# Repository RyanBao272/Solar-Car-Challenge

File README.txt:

SOLAR CAR TELEMETRY - SEAGULL SOLAR RACING

Live telemetry and low-voltage electronics for Staten Island Tech's solar
car at the 2026 Solar Car Challenge in Texas.

Result: 2nd place, Classic Division - 2026 Solar Car Challenge (460 miles)

HOW THE TELEMETRY WORKS
Motor controller --> Teensy 4.1 --> ESP32 --> driver LCD + Wi-Fi dashboard

code/teensyfulltelemtry
  - Reads the Fardriver motor controller over UART (19200 baud)
  - Decodes RPM, battery voltage, and current from its binary frames
  - Calculates speed and battery % from the controller's settings
  - Sends the data to the ESP32 as JSON 10 times a second

code/esp32telemetrydisplay
  - Shows the data on the driver's LCD in the steering wheel
  - Hosts a Wi-Fi dashboard that updates live over a WebSocket

CAR LOW-VOLTAGE SYSTEM (kicad-schematics/)
Full schematic: kicad-schematics/solar schematic.pdf

  - 24V aux battery, fuse block, 24V to 5V converter, fan, camera
  - Disconnect switches and contactors for the 96V motor and solar array
  - Front and back Arduinos talking over CAN for lights, horn, and signals

Telemetry PCB: teensy.kicad_sch / teensy.kicad_pcb
  (Teensy 4.1, ESP32, RS485-to-TTL converter, buck converter)

PHOTOS AND VIDEOS
See the images/ folder.

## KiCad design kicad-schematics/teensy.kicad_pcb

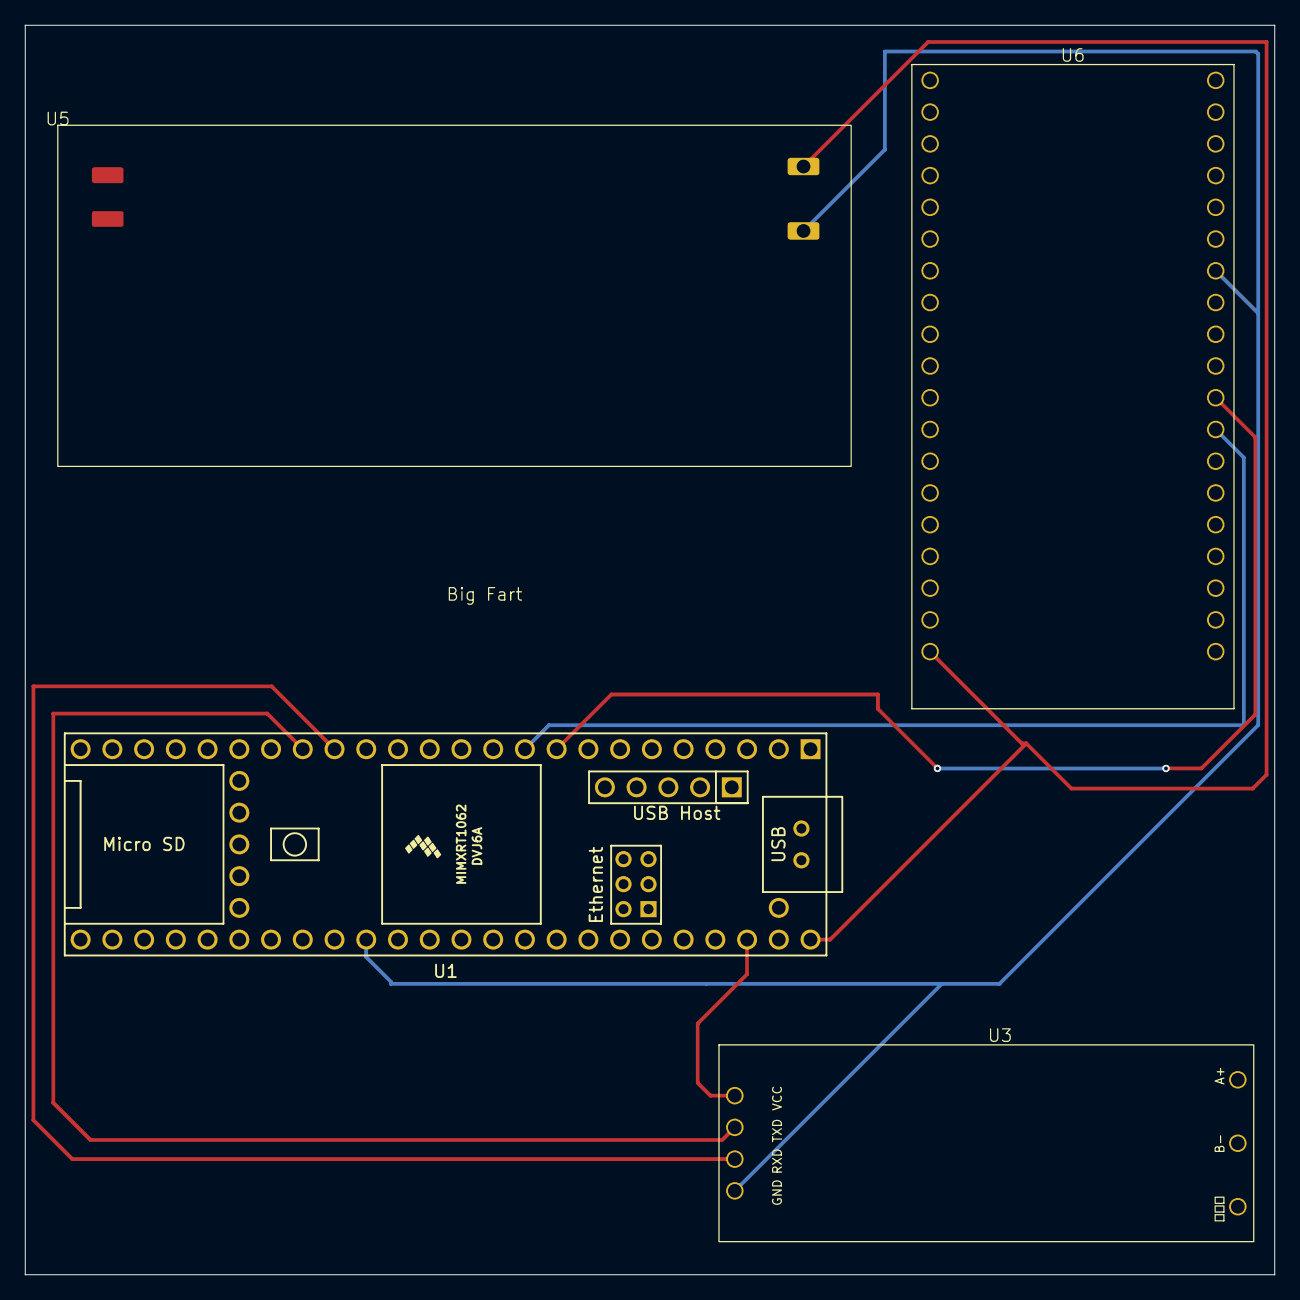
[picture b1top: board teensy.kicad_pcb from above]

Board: 2 copper layers, 100.0 x 100.0 mm, 4 parts (0 on the bottom side), 7 nets.

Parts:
U1: Teensy4.1; Teensy41
U3: RS485_TO_TTL
U5: LM2596_Module; Buck Converter
U6: ESP32-DEVKITC-32E; ESP32_Real

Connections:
+3V3: U1.46 (3V3), U3.7 (VCC)
/TEENSY_RX2: U1.9 (7_RX2_OUT1A), U6.28 (IO17)
/TEENSY_RX6: U1.17 (25_A11_RX6_SDA2), U3.6 (TXD)
/TEENSY_TX2: U1.10 (8_TX2_IN1), U6.27 (IO16)
/TEENSY_TX6: U1.16 (24_A10_TX6_SCL2), U3.5 (RXD)
/Vout+: U1.48 (VIN), U5.1 (Vout+), U6.19 (EXT_5V)
GND: U1.34 (GND), U3.4 (GND), U5.2 (Vout-), U6.32 (GND_J3_7)
